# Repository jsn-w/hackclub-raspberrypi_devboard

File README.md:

# hackclub-raspberrypi_devboard
The hackclub-raspberrypi_devboard is a custom development board designed to be simple and easy to use, similar to an Arduino, but build with a RaspberryPi microcontroller.
There are many features, such as compatibility with USB-C, supports breadboard pitch, and works with different software (Arduino, CircuitPython, etc).

# Features, materials
- 29 GPIO pins (4 of them are also ADC)
- Voltage Regulator
- 12 MHz crystal oscillator
- External flash chip

# Schematic!

# PCB
The PCB was made within KiCad and has two layers, where the top and bottom layer both connect to GND. It would be beneficial to have a four layer PCB instead of two since the routings would be done easier by setting adding another power plane for 3.3V or VCC.

<p>There are currently errors for the flash chip since it was imported. The pads are too close to each other but I couldn't find a way to edit them.</p>

# Materials Used
- 1x USB_C_Receptacle_USB2.0_14P
- 1x MCP1700x-330xxTT
- 1x W25Q16JVUXIQ_TR
- 1x Crystal_SMD_3225
- 2x 01x20 pin connector
- 1x 01x03 pin connector
Capacitors
- 11x 100nF
- 2x  1uF
- 2x  10uF
- 2x  33pF
Resistors
- 4x 1.5k
- 1x 1k
- 2x 27

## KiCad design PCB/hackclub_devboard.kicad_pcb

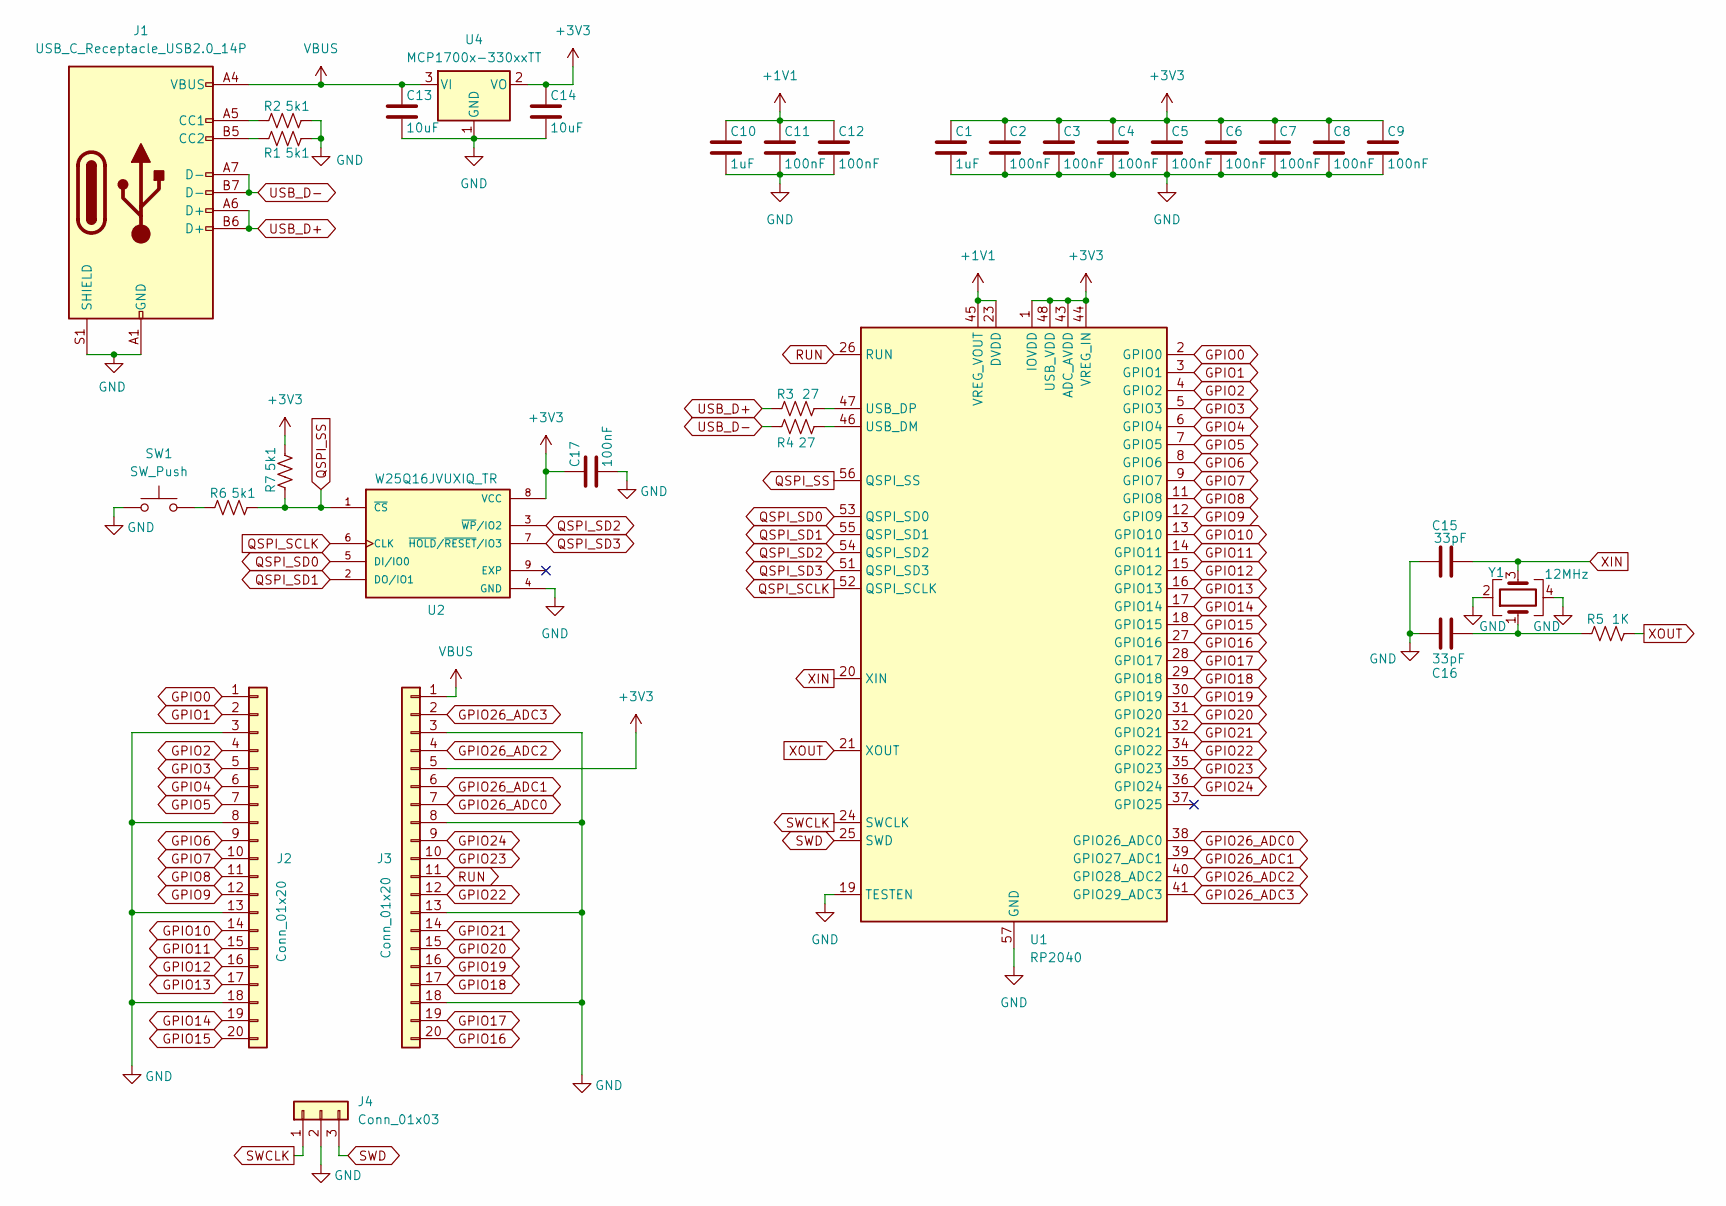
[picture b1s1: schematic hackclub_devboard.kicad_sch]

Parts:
C1, C10: 1uF; C_0402_1005Metric
C2, C3, C4, C5, C6, C7, C8, C9, C11, C12, C17: 100nF; C_0402_1005Metric
C13, C14: 10uF; C_0603_1608Metric
C15, C16: 33pF; C_0402_1005Metric
J1: USB_C_Receptacle_USB2.0_14P; USB_C_Receptacle_HRO_TYPE-C-31-M-12
J2, J3: Conn_01x20; PinHeader_1x20_P2.54mm_Vertical
J4: Conn_01x03; PinHeader_1x03_P2.54mm_Vertical
R1, R2, R6, R7: 5k1; R_0402_1005Metric
R3, R4: 27; R_0402_1005Metric
R5: 1K; R_0402_1005Metric
SW1: SW_Push; Crystal_SMD_3225-4Pin_3.2x2.5mm
U1: RP2040; QFN-56-1EP_7x7mm_P0.4mm_EP3.2x3.2mm
U2: W25Q16JVUXIQ_TR; IC_W25Q16JVUXIQ_TR; PARTREV H
U4: MCP1700x-330xxTT; SOT-23
Y1: 12MHz; Crystal_SMD_3225-4Pin_3.2x2.5mm

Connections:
+1V1: C10.1, C11.1, C12.1, U1.23 (DVDD), U1.45 (VREG_VOUT), U1.50 (DVDD)
+3V3: C1.1, C2.1, C3.1, C4.1, C5.1, C6.1, C7.1, C8.1, C9.1, C14.1, C17.1, J3.5, R7.2, U1.1 (IOVDD), U1.10 (IOVDD), U1.22 (IOVDD), U1.33 (IOVDD), U1.42 (IOVDD), U1.43 (ADC_AVDD), U1.44 (VREG_IN), U1.48 (USB_VDD), U1.49 (IOVDD), U2.8 (VCC), U4.2 (VO)
GND: C1.2, C2.2, C3.2, C4.2, C5.2, C6.2, C7.2, C8.2, C9.2, C10.2, C11.2, C12.2, C13.2, C14.2, C15.1, C16.1, C17.2, J1.A1 (GND), J1.A12 (GND), J1.B1 (GND), J1.B12 (GND), J1.S1 (SHIELD), J2.3, J2.8, J2.13, J2.18, J3.3, J3.8, J3.13, J3.18, J4.2, R1.2, R2.2, SW1.1, U1.19 (TESTEN), U1.57 (GND), U2.4 (GND), U4.1 (GND), Y1.2, Y1.4
GPIO0: J2.1, U1.2 (GPIO0)
GPIO1: J2.2, U1.3 (GPIO1)
GPIO2: J2.4, U1.4 (GPIO2)
GPIO3: J2.5, U1.5 (GPIO3)
GPIO4: J2.6, U1.6 (GPIO4)
GPIO5: J2.7, U1.7 (GPIO5)
GPIO6: J2.9, U1.8 (GPIO6)
GPIO7: J2.10, U1.9 (GPIO7)
GPIO8: J2.11, U1.11 (GPIO8)
GPIO9: J2.12, U1.12 (GPIO9)
GPIO10: J2.14, U1.13 (GPIO10)
GPIO11: J2.15, U1.14 (GPIO11)
GPIO12: J2.16, U1.15 (GPIO12)
GPIO13: J2.17, U1.16 (GPIO13)
GPIO14: J2.19, U1.17 (GPIO14)
GPIO15: J2.20, U1.18 (GPIO15)
GPIO16: J3.20, U1.27 (GPIO16)
GPIO17: J3.19, U1.28 (GPIO17)
GPIO18: J3.17, U1.29 (GPIO18)
GPIO19: J3.16, U1.30 (GPIO19)
GPIO20: J3.15, U1.31 (GPIO20)
GPIO21: J3.14, U1.32 (GPIO21)
GPIO22: J3.12, U1.34 (GPIO22)
GPIO23: J3.10, U1.35 (GPIO23)
GPIO24: J3.9, U1.36 (GPIO24)
GPIO26_ADC0: J3.7, U1.38 (GPIO26_ADC0)
GPIO26_ADC1: J3.6, U1.39 (GPIO27_ADC1)
GPIO26_ADC2: J3.4, U1.40 (GPIO28_ADC2)
GPIO26_ADC3: J3.2, U1.41 (GPIO29_ADC3)
unnamed: C16.2, R5.1, Y1.1
unnamed: J1.A5 (CC1), R2.1
unnamed: J1.B5 (CC2), R1.1
unnamed: R6.1, SW1.2
unnamed: R4.1, U1.46 (USB_DM)
unnamed: R3.2, U1.47 (USB_DP)
QSPI_SCLK: U1.52 (QSPI_SCLK), U2.6 (CLK)
QSPI_SD0: U1.53 (QSPI_SD0), U2.5 (DI/IO0)
QSPI_SD1: U1.55 (QSPI_SD1), U2.2 (DO/IO1)
QSPI_SD2: U1.54 (QSPI_SD2), U2.3 (~WP/IO2)
QSPI_SD3: U1.51 (QSPI_SD3), U2.7 (~HOLD/~RESET/IO3)
QSPI_SS: R6.2, R7.1, U1.56 (QSPI_SS), U2.1 (~CS)
RUN: J3.11, U1.26 (RUN)
SWCLK: J4.1, U1.24 (SWCLK)
SWD: J4.3, U1.25 (SWD)
USB_D+: J1.A6 (D+), J1.B6 (D+), R3.1
USB_D-: J1.A7 (D-), J1.B7 (D-), R4.2
VBUS: C13.1, J1.A4 (VBUS), J1.A9 (VBUS), J1.B4 (VBUS), J1.B9 (VBUS), J3.1, U4.3 (VI)
XIN: C15.2, U1.20 (XIN), Y1.3
XOUT: R5.2, U1.21 (XOUT)

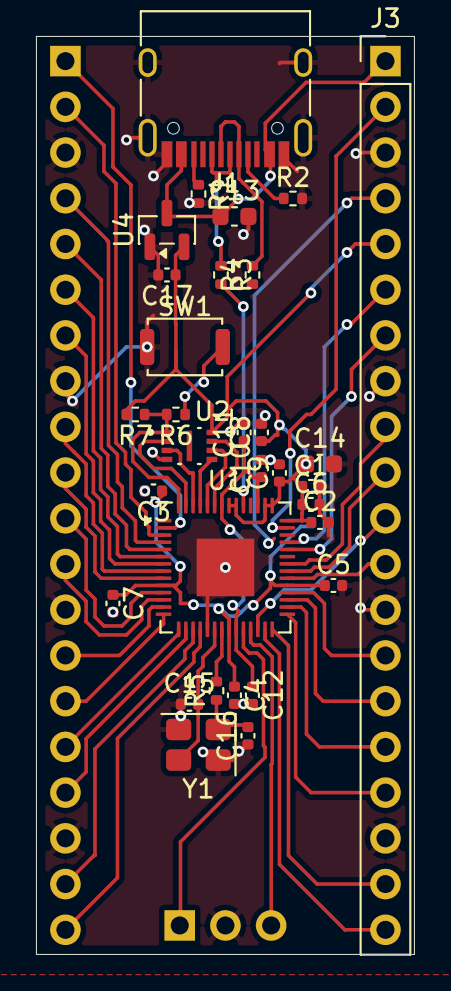
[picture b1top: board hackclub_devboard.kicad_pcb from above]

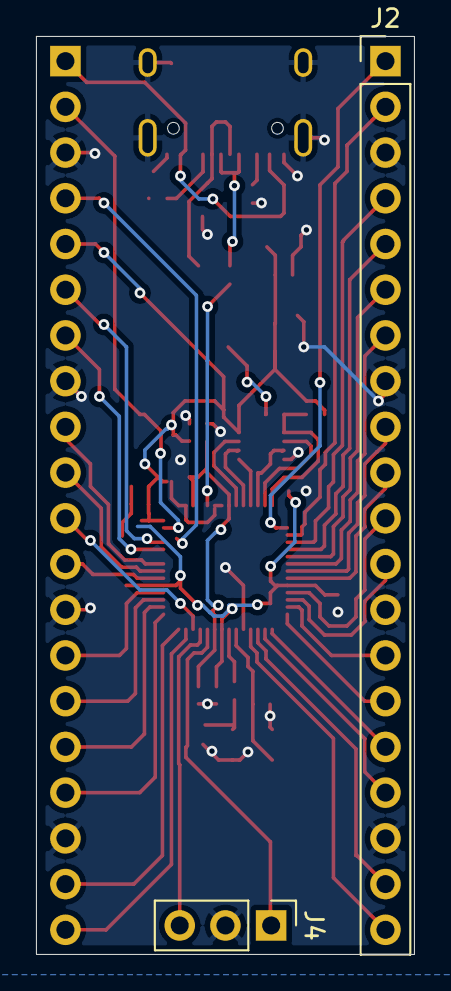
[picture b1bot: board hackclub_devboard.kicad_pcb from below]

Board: 2 copper layers, 21.0 x 51.0 mm, 33 parts (2 on the bottom side), 52 nets.

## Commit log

2025-12-05 Enhance README with project details and materials
    Added detailed description, features, and materials for the hackclub-raspberrypi_devboard.
2025-12-05 Add journal entry for PCB wiring and tracing
    Documented the process of wiring the schematic and tracing the PCB, including images and insights on component placement and routing challenges.
2025-12-05 Enhance JOURNAL.md with formatting and details
    Updated the journal with improved formatting and additional explanations about wiring and PCB design.
2025-12-05 Document firmware and PCB development progress
    Added journal entries detailing firmware development, schematic wiring, and PCB tracing processes.
2025-12-05 Update PCB section with new images and formatting
    Updated PCB images and fixed formatting issues in the README.
2025-12-05 Enhance README with PCB design information
    Added details about the PCB design and its limitations.
2025-12-05 Revise PCB section in README with images and notes
    Updated PCB section with additional images and notes on design limitations.
